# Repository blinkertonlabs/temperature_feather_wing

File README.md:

# Temperature Feather Wing
Feather Wing to measure temperature and humidity, while enabling sleep mode on a Feather controller board.

This project is really a mashup of several other existing projects.  
http://www.blinkertonlabs.com/wireless-temperature-monitor.html

The main goals of this Feather Wing are as follows.
* Measure temperature and humidity using a [DHT11 or DHT22](https://learn.adafruit.com/dht) sensor
* Allow for the Feather controller to sleep/wake
* Measure the battery voltage to estimate the remaining power

The DHT sensor was chosen to keep costs down.  
Ideally, a user could distribute one of these sensors in each room of their living space to record how efficiently the heating/cooling energy is being ditribited.  Then, as energy efficientcy changes are made, the user could see the results and track their effectiveness.

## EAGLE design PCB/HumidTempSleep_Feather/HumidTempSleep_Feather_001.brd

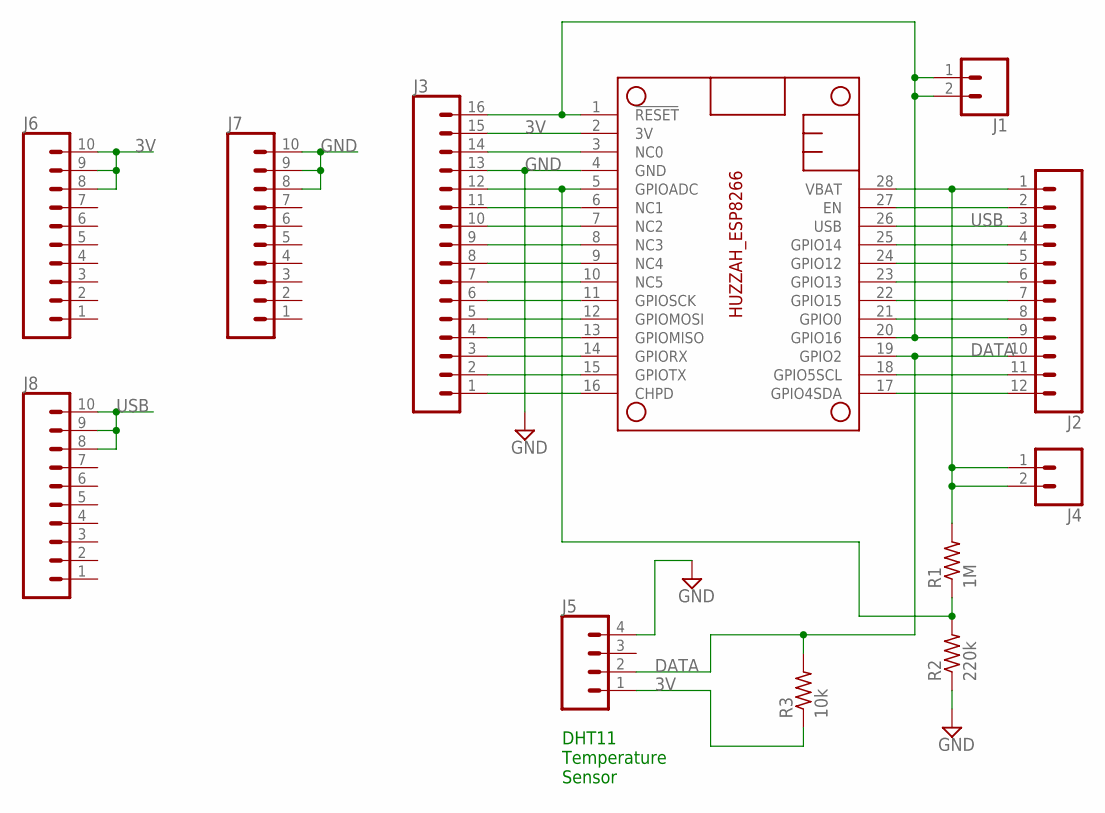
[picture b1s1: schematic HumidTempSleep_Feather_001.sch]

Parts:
J1, J4: CONN_02; 1X02
J2: CONN_12; 1X12
J3: CONN_16; 1X16
J5: CONN_04PTH; 1X04
J6, J7, J8: CONN_10"; 1X10
MS2: FEATHERWING
R1: 1M; R0805
R2: 220k; R0805
R3: 10k; R0805

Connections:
3V: J3.15, J5.1, J6.8, J6.9, J6.10, MS2.2 (3V), R3.1
DATA: J2.10, J5.2, MS2.19 (GPIO2), R3.2
GND: J3.13, J5.4, J7.8, J7.9, J7.10, MS2.4 (GND), R2.1
unnamed: J1.1, J1.2, J2.9, J3.16, MS2.1 (!RESET), MS2.20 (GPIO16)
unnamed: J2.2, MS2.27 (EN)
unnamed: J2.4, MS2.25 (GPIO14)
unnamed: J2.5, MS2.24 (GPIO12)
unnamed: J2.6, MS2.23 (GPIO13)
unnamed: J2.7, MS2.22 (GPIO15)
unnamed: J2.8, MS2.21 (GPIO0)
unnamed: J2.11, MS2.18 (GPIO5SCL)
unnamed: J2.12, MS2.17 (GPIO4SDA)
unnamed: J3.14, MS2.3 (NC0)
unnamed: J3.11, MS2.6 (NC1)
unnamed: J3.10, MS2.7 (NC2)
unnamed: J3.9, MS2.8 (NC3)
unnamed: J3.8, MS2.9 (NC4)
unnamed: J3.7, MS2.10 (NC5)
unnamed: J3.6, MS2.11 (GPIOSCK)
unnamed: J3.5, MS2.12 (GPIOMOSI)
unnamed: J3.4, MS2.13 (GPIOMISO)
unnamed: J3.3, MS2.14 (GPIORX)
unnamed: J3.2, MS2.15 (GPIOTX)
unnamed: J3.1, MS2.16 (CHPD)
unnamed: J3.12, MS2.5 (GPIOADC), R1.1, R2.2
USB: J2.3, J8.8, J8.9, J8.10, MS2.26 (USB)
VBAT: J2.1, J4.1, J4.2, MS2.28 (VBAT), R1.2

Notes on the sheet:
DHT11 Temperature Sensor

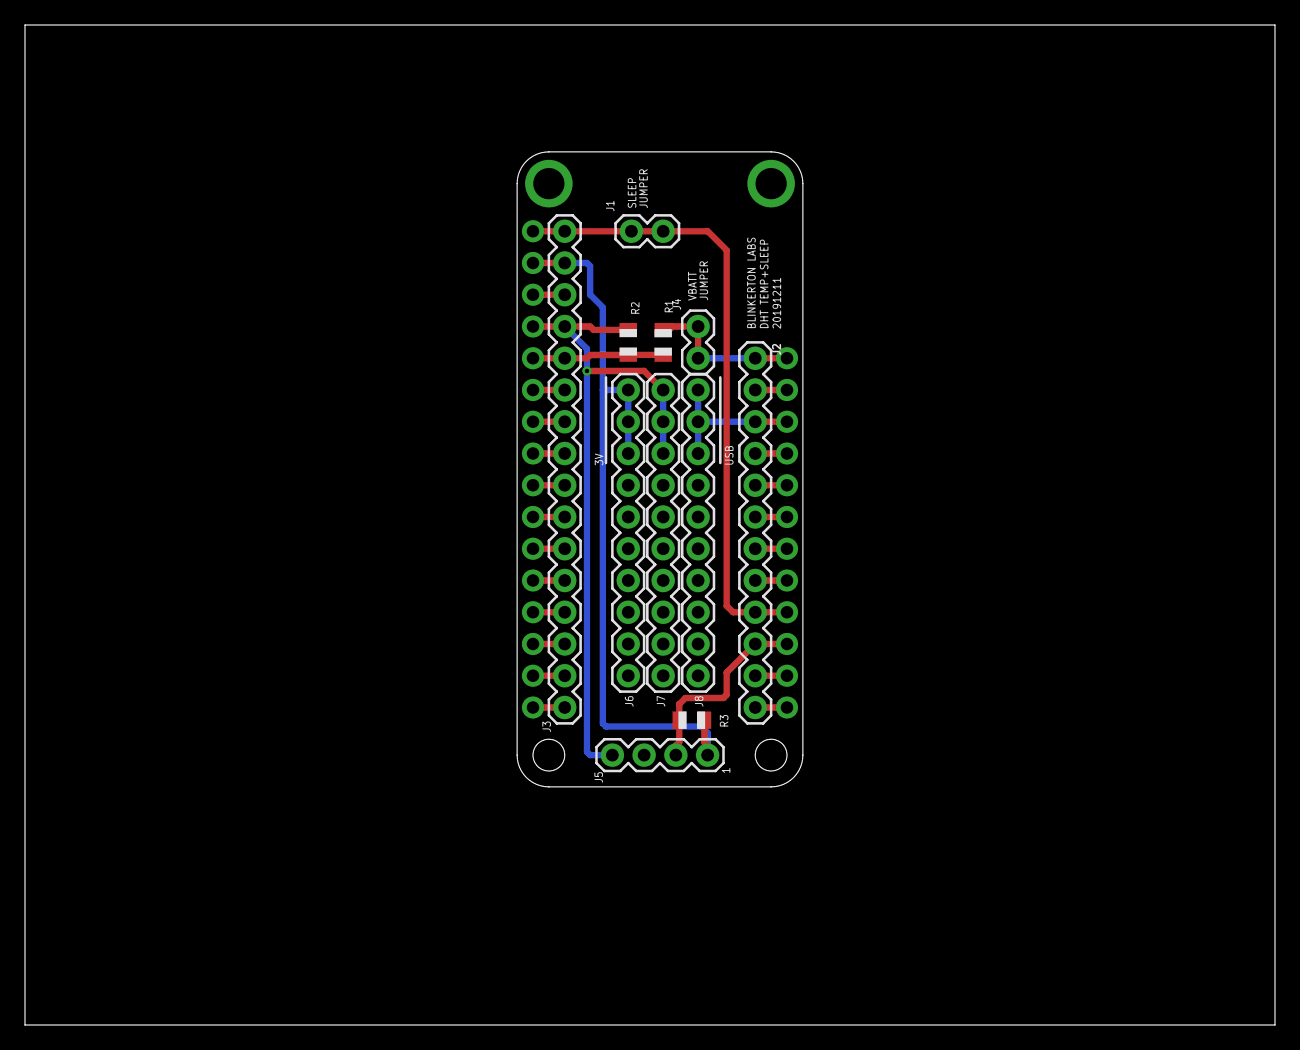
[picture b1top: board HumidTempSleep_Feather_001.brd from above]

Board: 2 copper layers, 100.0 x 80.0 mm, 12 parts (0 on the bottom side), 27 nets.

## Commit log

2019-11-19 Added information to the README from inception.
2019-11-19 Added the Feather code
    Added the Feather code, which has been logging data since 03/2019.
2019-11-20 Created the PCB schematic and custom library
    Created the PCB schematic.
    Had to create a custom library and symbol since the pin names on the existing FEATHER_WING device did not match up with the HUZZAH ESP8266 Feather Board. https://www.adafruit.com/product/2821
2019-11-21 Added some jumpers
    Added the jumpers for turning off the reset and the batery monitoring.
    Also put on some jumpers to parallel the connections to the Feather.
2019-12-03 Finished schematic and added PCB
2019-12-07 Vbatt jumper and layout
    Moved the jumper for the vbatt trace, and completed most of the layout.
2019-12-12 Added prototype jumpers
2019-12-14 Changing to the MIT license.
2019-12-14 Added some more information to the README
    More about the goal of the project.
2019-12-14 Ignore more Eagle files
    This should remove layout backup files.

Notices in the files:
parts and their libraries:
SparkFun-Connectors: Licensing: Creative Commons ShareAlike 4.0 International - https://creativecommons.org/licenses/by-sa/4.0
